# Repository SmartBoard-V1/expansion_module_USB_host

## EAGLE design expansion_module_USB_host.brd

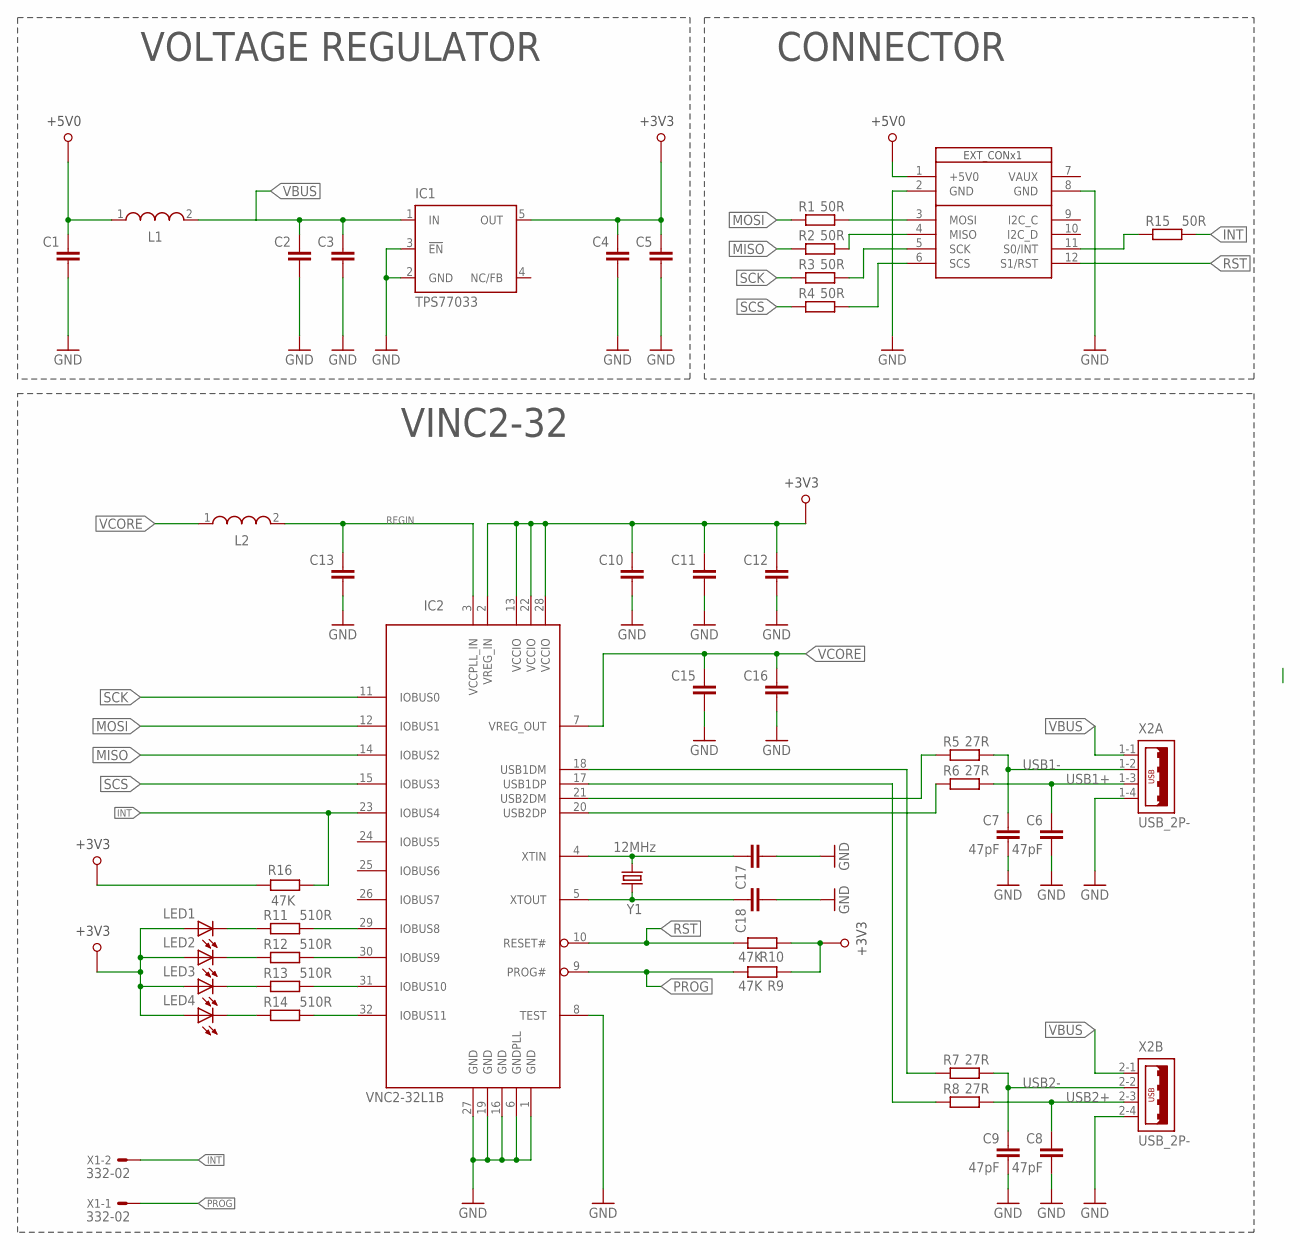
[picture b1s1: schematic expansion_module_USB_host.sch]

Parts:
C1, C2, C3, C4, C5, C10, C11, C12, C13, C15, C16, C17, C18: C-EUC0805; C0805
C6, C7, C8, C9: 47pF; C0805
IC1: TPS77033; SOT23-DBV
IC2: VNC2-32L1B; LQFP32
L1, L2: WE-LQ_1210; WE-LQ_M
LED1, LED2, LED3, LED4: LEDCHIPLED_0805; CHIPLED_0805
R1, R2, R3, R4, R15: 50R; R0805
R5, R6, R7, R8: 27R; R0805
R9, R10, R16: 47K; R0805
R11, R12, R13, R14: 510R; R0805
U$1: SB_EXT_CON_X1_SPI; SB_EXT_CON_X1_FULL
X1: 332-02
X2: USB_2P-; 85-32003-00X-1_DUAL
Y1: 12MHz; CRYSTAL-SMD-5X3

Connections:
+3V3: C4.2, C5.2, C10.2, C11.2, C12.2, IC1.5 (OUT), IC2.2 (VREG_IN), IC2.13 (VCCIO), IC2.22 (VCCIO), IC2.28 (VCCIO), LED1.A, LED2.A, LED3.A, LED4.A, R9.1, R10.1, R16.2
+5V0: C1.2, L1.1, U$1.1 (+5V0)
GND: C1.1, C2.1, C3.1, C4.1, C5.1, C6.1, C7.1, C8.1, C9.1, C10.1, C11.1, C12.1, C13.1, C15.1, C16.1, C17.1, C18.1, IC1.2 (GND), IC1.3 (!EN), IC2.1 (GND), IC2.6 (GNDPLL), IC2.8 (TEST), IC2.16 (GND), IC2.19 (GND), IC2.27 (GND), U$1.2 (GND), U$1.8 (GND), X2.1-4 (4), X2.2-4 (4)
INT: IC2.23 (IOBUS4), R15.2, R16.1, X1.2
MISO: IC2.14 (IOBUS2), R2.1
MOSI: IC2.12 (IOBUS1), R1.1
unnamed: R1.2, U$1.3 (MOSI)
unnamed: R2.2, U$1.4 (MISO)
unnamed: R3.2, U$1.5 (SCK)
unnamed: R4.2, U$1.6 (SCS)
unnamed: LED1.C, R11.1
unnamed: IC2.29 (IOBUS8), R11.2
unnamed: C17.2, IC2.4 (XTIN), Y1.1
unnamed: IC2.21 (USB2DM), R5.1
unnamed: C18.2, IC2.5 (XTOUT), Y1.3 (2)
unnamed: IC2.18 (USB1DM), R7.1
unnamed: IC2.17 (USB1DP), R8.1
unnamed: IC2.30 (IOBUS9), R12.2
unnamed: IC2.31 (IOBUS10), R13.2
unnamed: IC2.32 (IOBUS11), R14.2
unnamed: LED2.C, R12.1
unnamed: LED3.C, R13.1
unnamed: LED4.C, R14.1
unnamed: IC2.20 (USB2DP), R6.1
unnamed: R15.1, U$1.11 (S0/INT)
PROG: IC2.9 (PROG#), R9.2, X1.1
REGIN: C13.2, IC2.3 (VCCPLL_IN), L2.2
RST: IC2.10 (RESET#), R10.2, U$1.12 (S1/RST)
SCK: IC2.11 (IOBUS0), R3.1
SCS: IC2.15 (IOBUS3), R4.1
USB1+: C6.2, R6.2, X2.1-3 (3)
USB1-: C7.2, R5.2, X2.1-2 (2)
USB2+: C8.2, R8.2, X2.2-3 (3)
USB2-: C9.2, R7.2, X2.2-2 (2)
VBUS: C2.2, C3.2, IC1.1 (IN), L1.2, X2.1-1 (1), X2.2-1 (1)
VCORE: C15.2, C16.2, IC2.7 (VREG_OUT), L2.1

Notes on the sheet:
CONNECTOR
VOLTAGE REGULATOR
VINC2-32

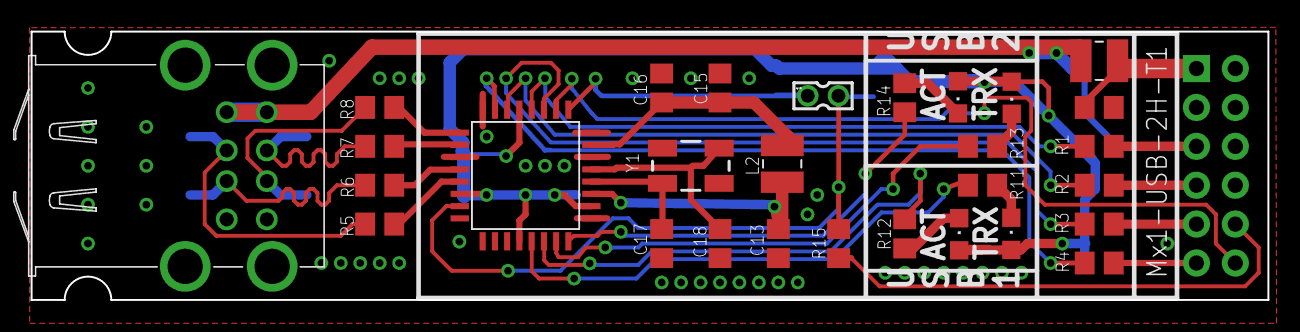
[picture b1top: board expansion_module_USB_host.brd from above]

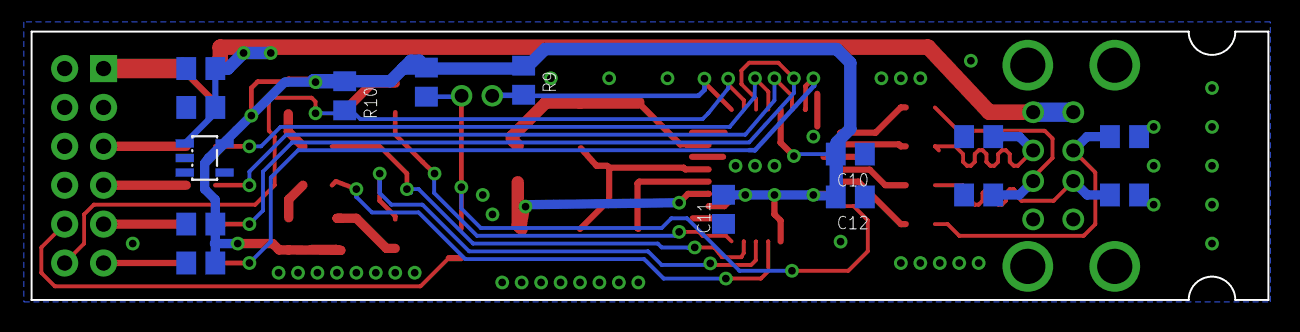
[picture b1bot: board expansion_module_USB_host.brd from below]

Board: 2 copper layers, 80.8 x 17.5 mm, 45 parts (15 on the bottom side), 36 nets.

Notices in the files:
parts and their libraries:
EagleLibrary_Wuerth_Elektronik_eiSos_rev: Copyright: Würth Elektronik
SparkFun-FreqCtrl: Licensing: Creative Commons ShareAlike 4.0 International - https://creativecommons.org/licenses/by-sa/4.0
